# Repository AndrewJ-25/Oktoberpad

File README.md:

# Oktoberpad

Oktoberpad is my macropad with 9 switches, a rotary encoder and an OLED display, designed following the guide published for Hackclub Blueprint. NOTE: the text and logo graphic on the silkcreen has been shifted upwards for better visibility.

## TODO:
  - code does not compile. have already identified several bugs

## Features:
  - 9 key layered keyboard
  - 0.91" OLED display
  - EC11 rotary encoder
  - 3D printed case

## CAD Model:
  - 3D printed case held together by 4 M3 bolts and heatset inserts
  - case designed in Onshape
  - PCB held to case using 4 M3 bolts and heatset inserts

## PCB:
  pcb designed in Kicad

  schematic:

  pcb:

## Firmware
  Oktoberpad uses QMK firmware

  - The rotary encoder adjusts volume, or cycles between keyboard layers when pressed and turned
  - OLED display indicates current layer
  - These layers are: emojis, music control, keyboard shortcuts, wechat sticker codes

## BOM

  - 9x Cherry MX Switches
  - 49x DSA Keycaps
  - 8x M3x5x4 Heatset inserts
  - 8x M3x16mm SHCS Bolts
  - 9x 1N4148 DO-35 Diodes.
  - 1x 0.91" 128x32 OLED Display
  - 1x EC11 Rotary Encoder
  - 1x XIAO RP2040
  - 1x Case (2 printed parts)

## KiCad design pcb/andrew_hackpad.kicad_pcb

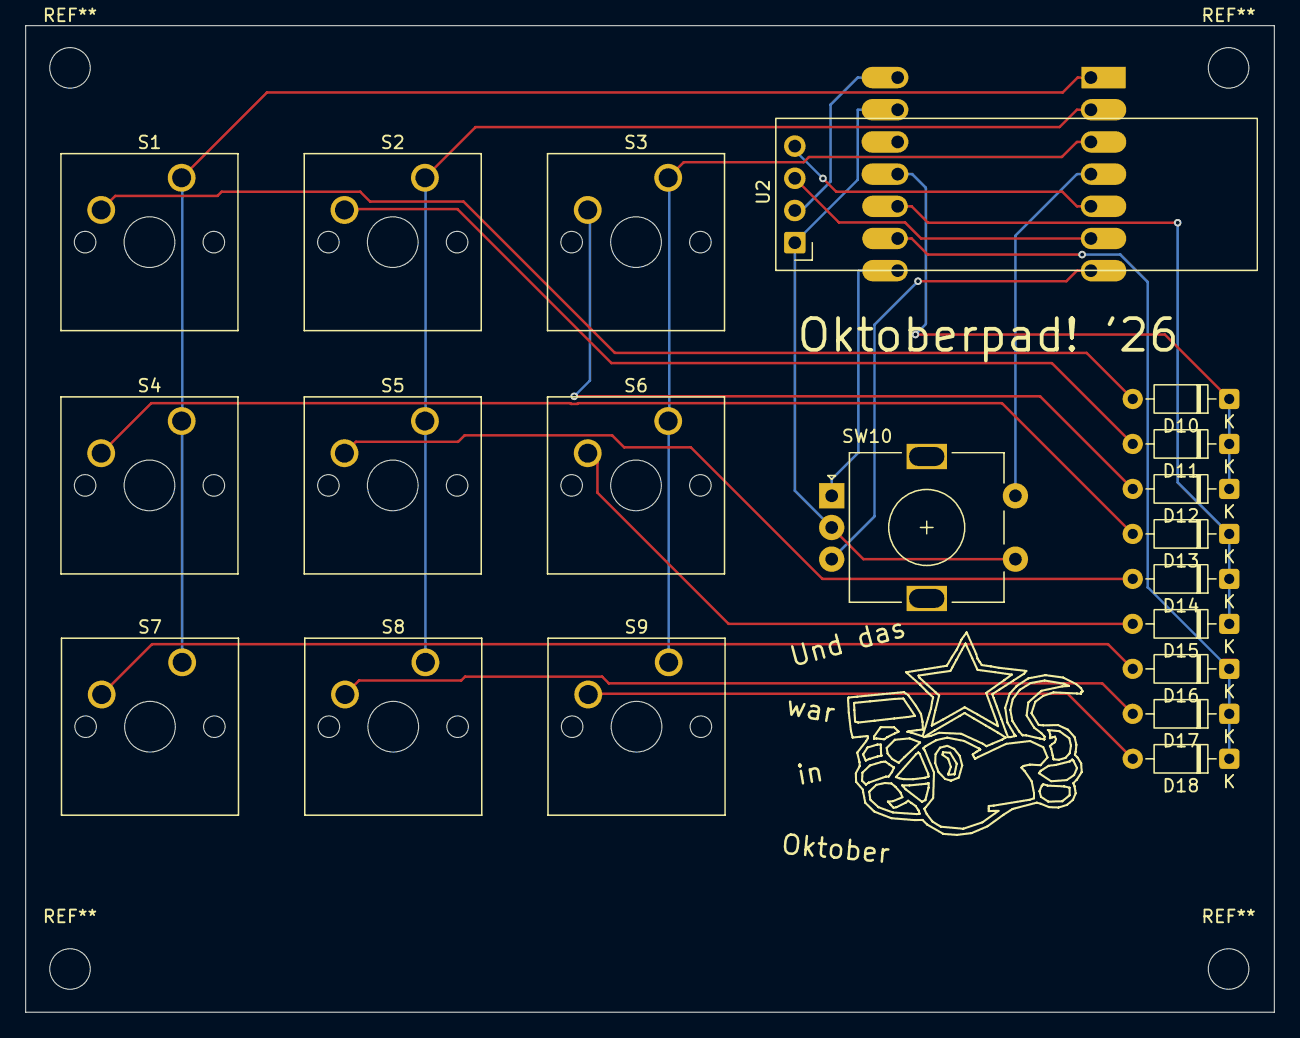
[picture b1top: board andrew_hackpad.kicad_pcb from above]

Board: 2 copper layers, 98.6 x 77.9 mm, 21 parts (1 on the bottom side), 22 nets.

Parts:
D10, D11, D12, D13, D14, D15, D16, D17, D18: 1N4148; D_DO-35_SOD27_P7.62mm_Horizontal
S1, S2, S3, S4, S5, S6, S7, S8, S9: SW_Cherry_MX_1.00u_PCB
SW10: RotaryEncoder_Switch; RotaryEncoder_Alps_EC11E-Switch_Vertical_H20mm
U1: MOUDLE-SEEEDUINO-XIAO; XIAO-Generic-Hybrid-14P-2.54-21X17.8MM
U2: ER_OLEDM0.91_1x-I2C

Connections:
Column 0: S1.1, S4.1, S7.1, U1.1 (PA02_A0_D0)
Column 1: S2.1, S5.1, S8.1, U1.2 (PA4_A1_D1)
Column 2: S3.1, S6.1, S9.1, U1.3 (PA10_A2_D2)
EC11A: SW10.A, U1.8 (PB09_A7_D7_RX)
EC11B: SW10.B, U1.7 (PB08_A6_D6_TX)
EC11SWA: SW10.S2, U1.4 (PA11_A3_D3)
GND: SW10.C, SW10.S1, U1.13 (GND), U2.1 (GND)
unnamed: D10.2 (A), S1.2
unnamed: D11.2 (A), S2.2
unnamed: D12.2 (A), S3.2
unnamed: D13.2 (A), S4.2
unnamed: D14.2 (A), S5.2
unnamed: D15.2 (A), S6.2
unnamed: D16.2 (A), S7.2
unnamed: D17.2 (A), S8.2
unnamed: D18.2 (A), S9.2
Row 0: D10.1 (K), D11.1 (K), D12.1 (K), U1.11 (PA6_A10_D10_MOSI)
Row 1: D13.1 (K), D14.1 (K), D15.1 (K), U1.10 (PA5_A9_D9_MISO)
Row 2: D16.1 (K), D17.1 (K), D18.1 (K), U1.9 (PA7_A8_D8_SCK)
SCL: U1.6 (PA9_A5_D5_SCL), U2.3 (SCL)
SDA: U1.5 (PA8_A4_D4_SDA), U2.4 (SDA)
VCC: U1.14 (5V), U2.2 (VCC)

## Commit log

2026-03-28 Create placeholder
2026-03-31 Delete pcb/andrew_hackpad.kicad_sch
    replace with changed graphics
2026-03-31 Add files via upload
    new pcb: bird and text silkscreen moved upwards for better visibility
2026-05-19 edited cad
2026-05-19 added gitignore
2026-05-19 banished ds store
2026-05-19 tried to evict .history
